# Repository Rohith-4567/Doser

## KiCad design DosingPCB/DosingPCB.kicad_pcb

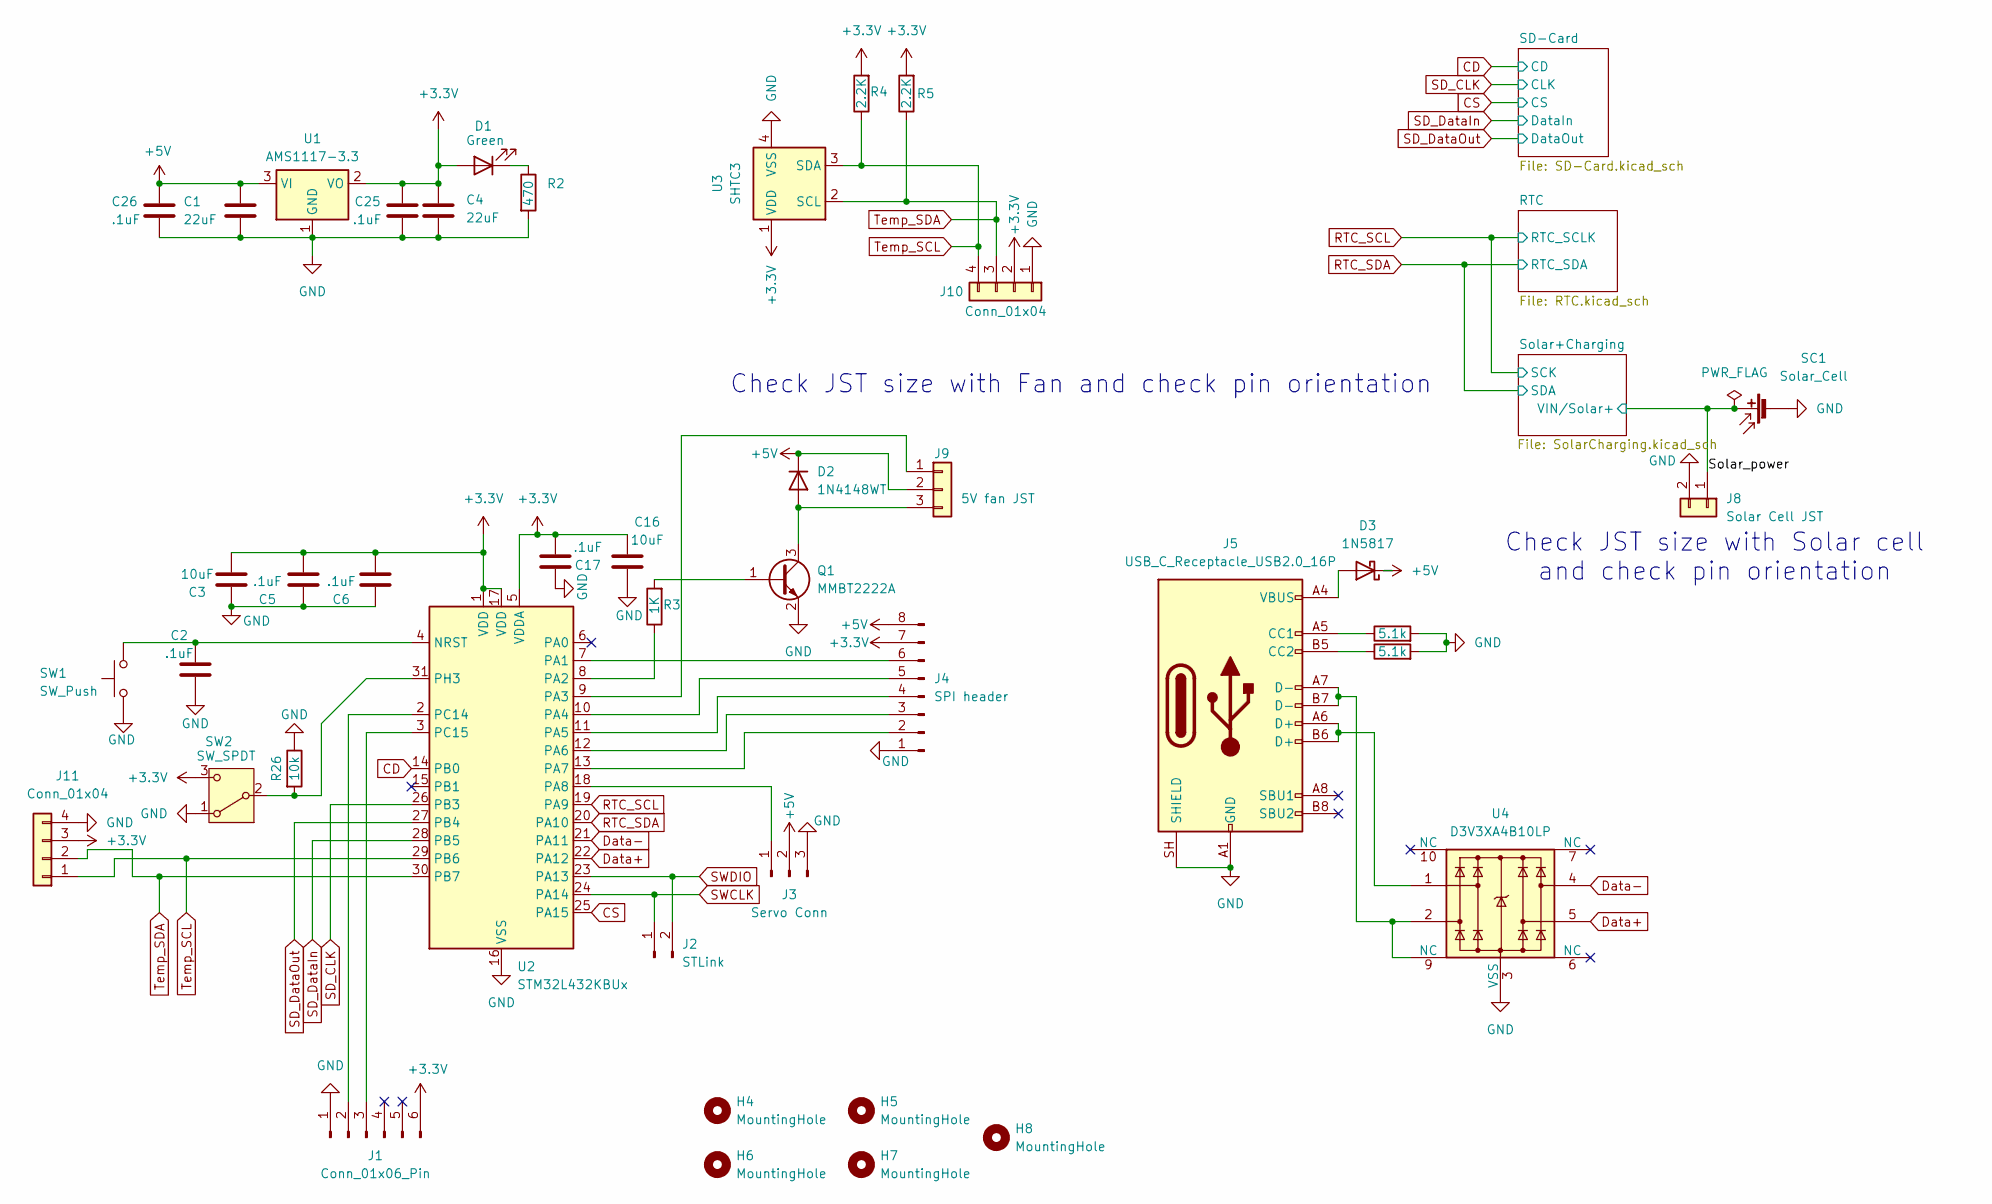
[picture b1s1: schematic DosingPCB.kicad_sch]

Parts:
C1, C4: 22uF; C_1206_3216Metric
C2, C5, C6, C17, C25, C26: .1uF; C_0603_1608Metric
C3, C16: 10uF; C_0805_2012Metric
D1: Green; LED_0603_1608Metric
D2: 1N4148WT; D_SOD-523
D3: 1N5817; D_SOD-123
H4, H5, H6, H7, H8: MountingHole; MountingHole_2.2mm_M2
J1: Conn_01x06_Pin; PinHeader_1x06_P2.54mm_Vertical
J2: STLink; PinHeader_1x02_P2.54mm_Vertical
J3: Servo Conn; PinHeader_1x03_P2.54mm_Horizontal
J4: SPI header; PinHeader_1x08_P2.54mm_Vertical
J5: USB_C_Receptacle_USB2.0_16P; USB_C_Receptacle_GCT_USB4105-xx-A_16P_TopMnt_Horizontal
J8: Solar Cell JST; JST_PH_S2B-PH-K_1x02_P2.00mm_Horizontal
J9: 5V fan JST; Molex_KK-254_AE-6410-03A_1x03_P2.54mm_Vertical
J10, J11: Conn_01x04; JST_SH_SM04B-SRSS-TB_1x04-1MP_P1.00mm_Horizontal
Q1: MMBT2222A; SOT-23
R2: 470; R_0805_2012Metric
R3: 1K; R_0805_2012Metric
R4, R5: 2.2K; R_0805_2012Metric
R6, R7: 5.1k; R_0805_2012Metric
R26: 10k; R_0805_2012Metric
SC1: Solar_Cell
SW1: SW_Push; SW_Push_SPST_NO_Alps_SKRK
SW2: SW_SPDT; SW_SPDT_PCM12
U1: AMS1117-3.3; SOT-223-3_TabPin2
U2: STM32L432KBUx; QFN-32-1EP_5x5mm_P0.5mm_EP3.45x3.45mm
U3: SHTC3; Sensirion_DFN-4-1EP_2x2mm_P1mm_EP0.7x1.6mm
U4: D3V3XA4B10LP; Diodes_UDFN-10_1x2.5mm_P0.5mm

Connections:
+3.3V: C3.1, C4.1, C5.1, C6.1, C16.2, C17.1, C25.1, D1.2 (A), J1.6, J4.7, J10.2, J11.3, R4.2, R5.2, SW2.3 (C), U1.2 (VO), U2.1 (VDD), U2.5 (VDDA), U2.17 (VDD), U3.1 (VDD); also elsewhere on the board
+5V: C1.1, C26.1, D2.1 (K), D3.1 (K), J3.2, J4.8, J9.2, U1.3 (VI); also elsewhere on the board
/Solar_power: J8.1, SC1.1 (+); also elsewhere on the board
CD: U2.14 (PB0); also elsewhere on the board
CS: U2.25 (PA15); also elsewhere on the board
Data+: U2.22 (PA12), U4.5
Data-: U2.21 (PA11), U4.4
GND: C1.2, C2.1, C3.2, C4.2, C5.2, C6.2, C16.1, C17.2, C25.2, C26.2, J1.1, J3.3, J4.1, J5.A1 (GND), J5.A12 (GND), J5.B1 (GND), J5.B12 (GND), J5.SH (SHIELD), J8.2, J10.1, J11.4, Q1.2 (E), R2.2, R6.2, R7.2, R26.1, SC1.2 (-), SW1.1, SW2.1 (A), U1.1 (GND), U2.16 (VSS), U2.32 (VSS), U2.33 (VSS), U3.4 (VSS), U4.3 (VSS), U4.8 (VSS); also elsewhere on the board
unnamed: D1.1 (K), R2.1
unnamed: D2.2 (A), J9.3, Q1.3 (C)
unnamed: D3.2 (A), J5.A4 (VBUS), J5.A9 (VBUS), J5.B4 (VBUS), J5.B9 (VBUS)
unnamed: J1.2, U2.2 (PC14)
unnamed: J1.3, U2.3 (PC15)
unnamed: J3.1, U2.18 (PA8)
unnamed: J4.2, U2.13 (PA7)
unnamed: J4.3, U2.12 (PA6)
unnamed: J4.4, U2.11 (PA5)
unnamed: J4.5, U2.10 (PA4)
unnamed: J4.6, U2.7 (PA1)
unnamed: J5.A5 (CC1), R6.1
unnamed: J5.B5 (CC2), R7.1
unnamed: J5.A6 (D+), J5.B6 (D+), U4.1
unnamed: J5.A7 (D-), J5.B7 (D-), U4.2, U4.9 (NC)
unnamed: J9.1, U2.9 (PA3)
unnamed: Q1.1 (B), R3.2
unnamed: R26.2, SW2.2 (B), U2.31 (PH3)
unnamed: C2.2, SW1.2, U2.4 (NRST)
unnamed: R3.1, U2.8 (PA2)
RTC_SCL: U2.19 (PA9); also elsewhere on the board
RTC_SDA: U2.20 (PA10); also elsewhere on the board
SD_CLK: U2.26 (PB3); also elsewhere on the board
SD_DataIn: U2.28 (PB5); also elsewhere on the board
SD_DataOut: U2.27 (PB4); also elsewhere on the board
SWCLK: J2.1, U2.24 (PA14)
SWDIO: J2.2, U2.23 (PA13)
Temp_SCL: J10.4, J11.1, R4.1, U2.29 (PB6), U3.3 (SDA)
Temp_SDA: J10.3, J11.2, R5.1, U2.30 (PB7), U3.2 (SCL)

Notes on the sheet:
Check JST size with Solar cell and check pin orientation
Check JST size with Fan and check pin orientation

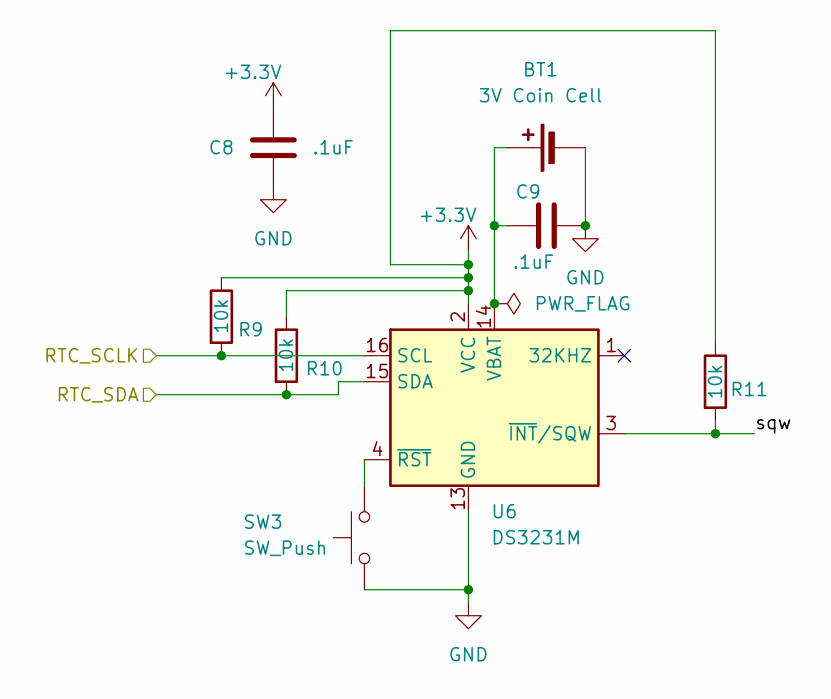
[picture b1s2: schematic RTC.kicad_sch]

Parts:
BT1: 3V Coin Cell; BatteryHolder_Keystone_3002_1x2032
C8, C9: .1uF; C_0603_1608Metric
R9, R10, R11: 10k; R_0805_2012Metric
SW3: SW_Push; SW_Push_SPST_NO_Alps_SKRK
U6: DS3231M; SOIC-16W_7.5x10.3mm_P1.27mm

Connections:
+3.3V: C8.1, R9.1, R10.1, R11.1, U6.2 (VCC); also elsewhere on the board
/RTC/sqw: R11.2, U6.3 (~INT/SQW)
GND: BT1.2 (-), C8.2, C9.1, SW3.1, U6.13 (GND); also elsewhere on the board
unnamed: BT1.1 (+), C9.2, U6.14 (VBAT)
unnamed: SW3.2, U6.4 (~RST)
RTC_SCL: R9.2, U6.16 (SCL); also elsewhere on the board
RTC_SDA: R10.2, U6.15 (SDA); also elsewhere on the board

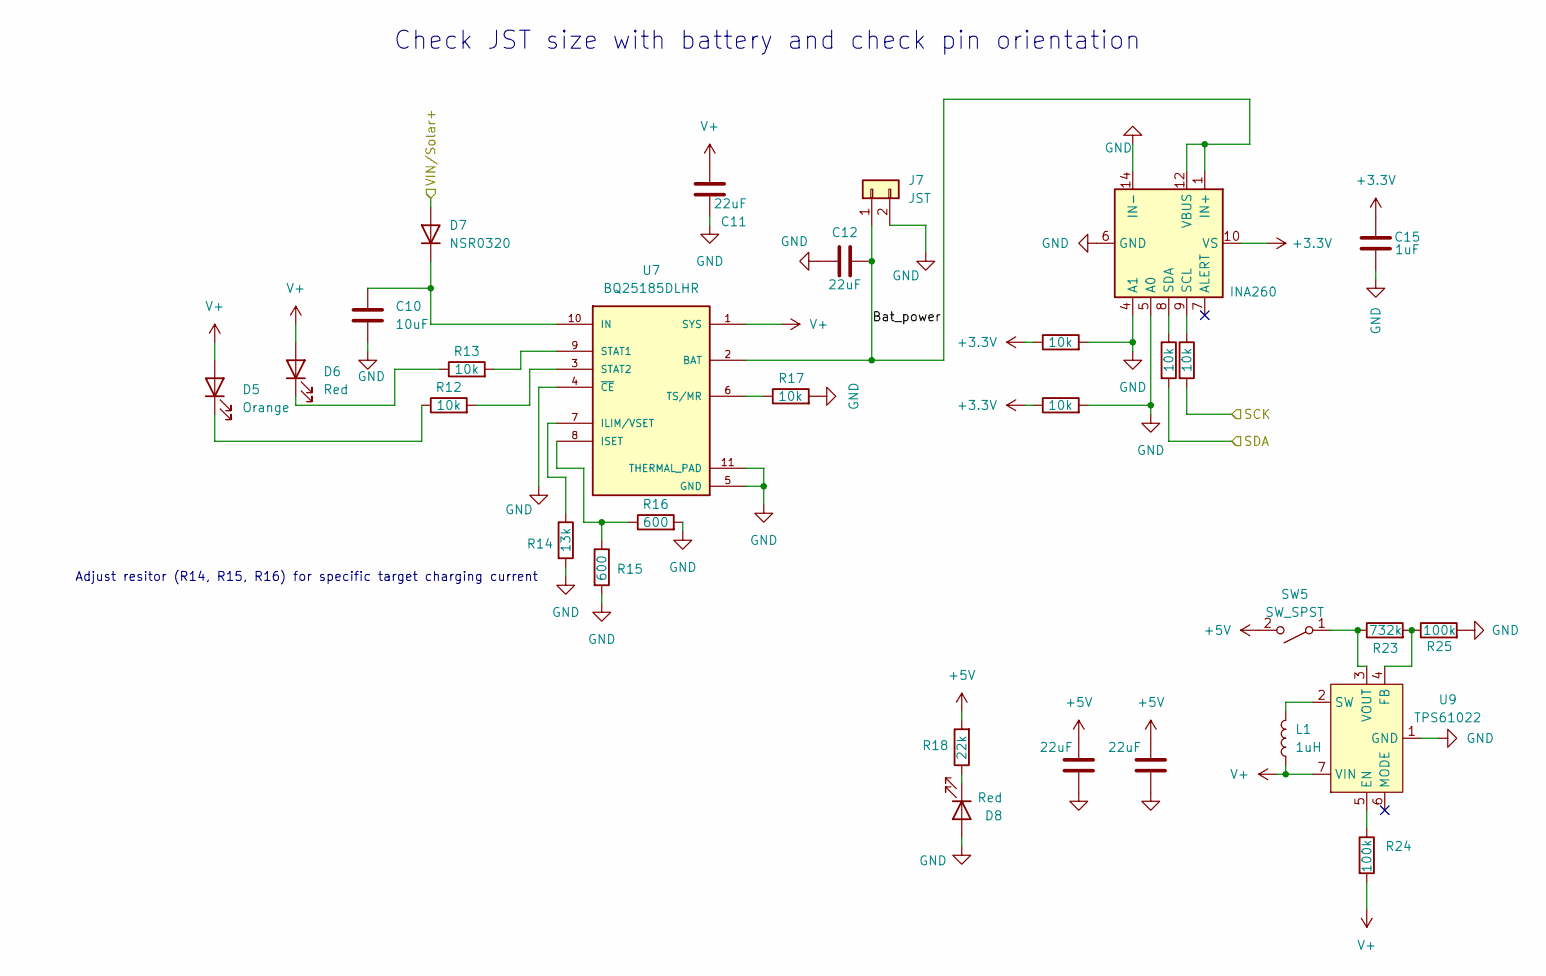
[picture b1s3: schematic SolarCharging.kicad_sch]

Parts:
C10: 10uF; C_0805_2012Metric
C11, C12, C13, C14: 22uF; C_1206_3216Metric
C15: 1uF; C_0603_1608Metric
D5: Orange; LED_0603_1608Metric
D6, D8: Red; LED_0603_1608Metric
D7: NSR0320; D_SOD-523
J7: JST; JST_PH_S2B-PH-K_1x02_P2.00mm_Horizontal
L1: 1uH; L_1210_3225Metric
R12, R13, R17, R19, R20, R21, R22: 10k; R_0805_2012Metric
R14: 13k; R_0805_2012Metric
R15, R16: 600; R_0805_2012Metric
R18: 22k; R_0805_2012Metric
R23: 732k; R_0805_2012Metric
R24, R25: 100k; R_0805_2012Metric
SW5: SW_SPST; SW_SPDT_PCM12
U7: BQ25185DLHR; IC_BQ25185DLHR; PARTREV OCTOBER 2023
U8: INA260; TSSOP-16_4.4x5mm_P0.65mm
U9: TPS61022; Texas_RWU0007A_VQFN-7_2x2mm_P0.5mm

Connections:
+3.3V: C15.1, R19.1, R20.1, U8.10 (VS); also elsewhere on the board
+5V: C13.2, C14.2, R18.2, SW5.2 (B); also elsewhere on the board
/Solar+Charging/Bat_power: C12.2, J7.1, U7.2 (BAT), U8.1 (IN+), U8.2 (IN+), U8.3 (IN+), U8.12 (VBUS)
/Solar_power: D7.2 (A); also elsewhere on the board
GND: C10.2, C11.1, C12.1, C13.1, C14.1, C15.2, D8.2 (A), J7.2, R14.2, R15.2, R16.2, R17.2, R19.2, R20.2, R25.2, U7.4 (~CE), U7.5 (GND), U7.11 (THERMAL_PAD), U7.12, U7.13, U8.4 (A1), U8.5 (A0), U8.6 (GND), U8.11 (GND), U8.14 (IN-), U8.15 (IN-), U8.16 (IN-), U9.1 (GND); also elsewhere on the board
unnamed: D5.1 (K), R12.1
unnamed: D6.1 (K), R13.1
unnamed: C10.1, D7.1 (K), U7.10 (IN)
unnamed: D8.1 (K), R18.1
unnamed: R23.1, SW5.1 (A), U9.3 (VOUT)
unnamed: R14.1, U7.7 (ILIM/VSET)
unnamed: R15.1, R16.1, U7.8 (ISET)
unnamed: R13.2, U7.9 (STAT1)
unnamed: R12.2, U7.3 (STAT2)
unnamed: R17.1, U7.6 (TS/MR)
unnamed: R22.1, U8.9 (SCL)
unnamed: R21.1, U8.8 (SDA)
unnamed: R24.1, U9.5 (EN)
unnamed: R23.2, R25.1, U9.4 (FB)
unnamed: L1.2, U9.2 (SW)
RTC_SCL: R22.2; also elsewhere on the board
RTC_SDA: R21.2; also elsewhere on the board
V+: C11.2, D5.2 (A), D6.2 (A), L1.1, R24.2, U7.1 (SYS), U9.7 (VIN)

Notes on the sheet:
Check JST size with battery and check pin orientation
Adjust resitor (R14, R15, R16) for specific target charging current

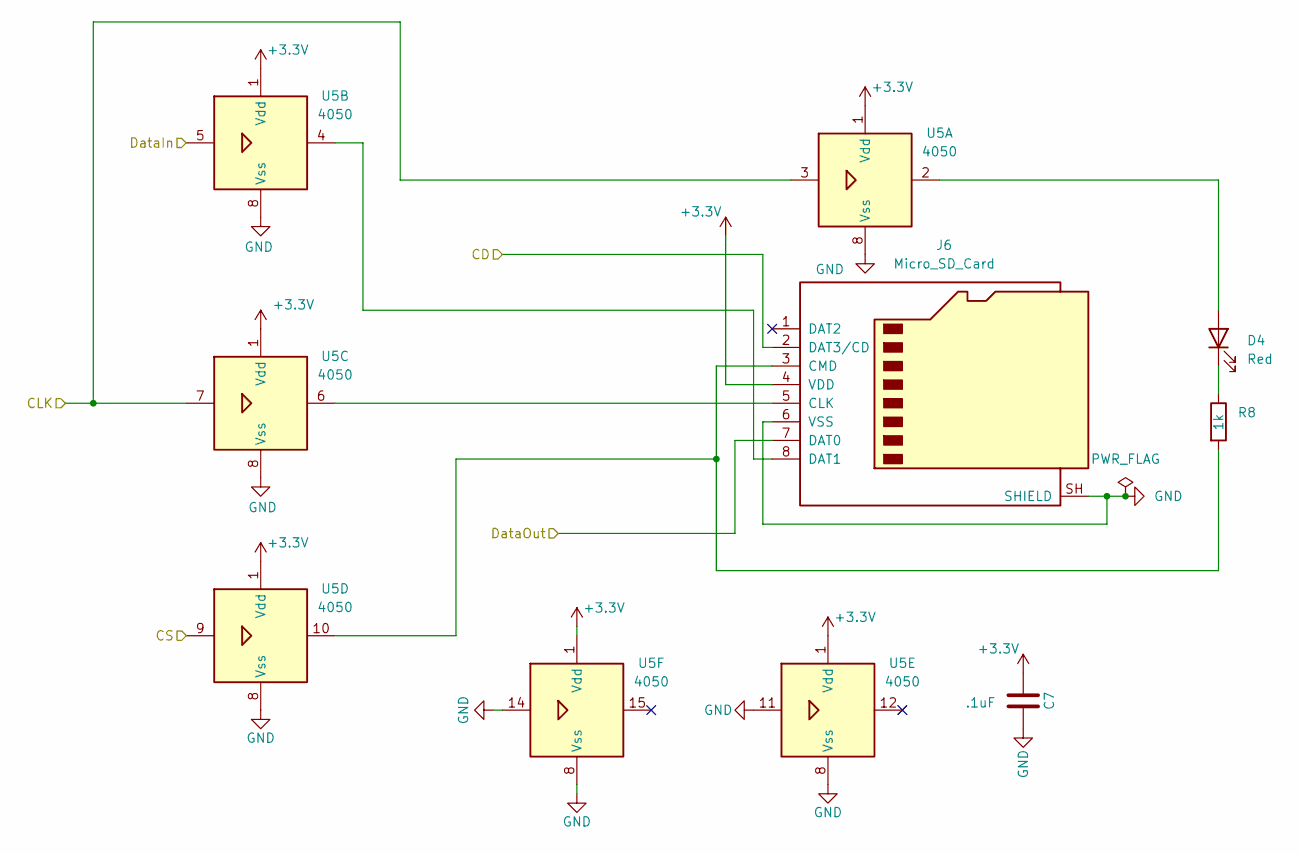
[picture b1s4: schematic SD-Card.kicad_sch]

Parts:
C7: .1uF; C_0603_1608Metric
D4: Red; LED_0603_1608Metric
J6: Micro_SD_Card; microSD_HC_Molex_104031-0811
R8: 1k; R_0805_2012Metric
U5: 4050; SOIC127P600X175-16N

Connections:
+3.3V: C7.1, J6.4 (VDD), U5.1 (Vdd); also elsewhere on the board
CD: J6.2 (DAT3/CD); also elsewhere on the board
CS: U5.9; also elsewhere on the board
GND: C7.2, J6.6 (VSS), J6.SH (SHIELD), U5.8 (Vss), U5.11, U5.14; also elsewhere on the board
unnamed: D4.2 (A), U5.2
unnamed: D4.1 (K), R8.1
unnamed: J6.5 (CLK), U5.6
unnamed: J6.3 (CMD), R8.2, U5.10
unnamed: J6.8 (DAT1), U5.4
SD_CLK: U5.3, U5.7; also elsewhere on the board
SD_DataIn: U5.5; also elsewhere on the board
SD_DataOut: J6.7 (DAT0); also elsewhere on the board

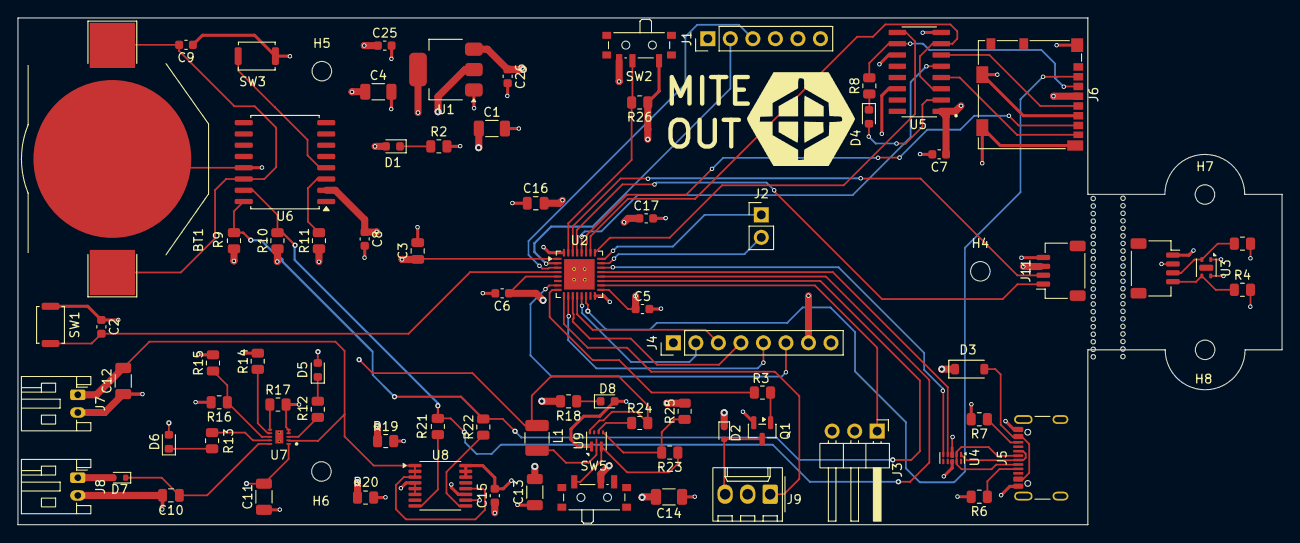
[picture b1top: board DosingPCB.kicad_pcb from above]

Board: 4 copper layers, 142.5 x 57.1 mm, 84 parts (0 on the bottom side), 62 nets.

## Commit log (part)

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2026-06-04 Initial setup
2026-06-12 Basically finished schematic
2026-06-13 Starting Board setup
2026-06-13 Quick RTC fix
2026-06-29 98% completed PCB
2026-06-30 Finished PCB - mousebites
2026-06-30 error fixes + logo
2026-06-30 errors+logo attempt 2
